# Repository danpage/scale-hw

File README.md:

# [SCALE](http://www.github.com/danpage/scale): hardware-oriented material

<!--- -------------------------------------------------------------------- --->

## Concept

The equipment used for a typical 
[side-channel attack](http://en.wikipedia.org/wiki/Side-channel_attack)
based on
[power analysis](http://en.wikipedia.org/wiki/Power_analysis)
might resemble the following:

```
                                                                   .... +-------------+
                                                                  /     | SCALE       |
+-------------+         +-------------+   trigger  +-------------+      | target      |
| control     |   USB   | acquisition | <--------- | target      |      | board       |
| platform    | <-----> | platform    |   signal   | platform    |      +-------------+
|             |         |             | <--------- |             |      | SCALE       |
+-------------+         +-------------+            +-------------+      | host        |
      ^                                                  ^        \     | board       |   
      |           USB                                    |         .... +-------------+
      +--------------------------------------------------+
```

The basic idea is that

- the target      platform represents the device under attack,
  or the
  [Device Under Test (DUT)](http://en.wikipedia.org/wiki/Device_under_test)
  in more common terms,

- the acquisition platform represents a   device, e.g., an
  [oscilloscope](http://en.wikipedia.org/wiki/Oscilloscope),
  to capture a signal from the target platform (under control of a trigger)
  and relay it to the control platform,

- the control     platform represents a workstation, which orchestrates the 
  attack by controlling the target and acquisition platforms: it will often
  repeat an acquisition loop, i.e.,

  - configure (e.g., fix the acquisition period) and initialise (e.g., arm 
    the trigger) the acquisition platform,
  - send    input     (e.g.,  plaintext) to   target      platform,
  - invoke  operation (e.g., encryption) on   target      platform,
  - receive output    (e.g., ciphertext) from target      platform,
    then,
  - receive trace                        from acquisition platform,

  to acquire a set of traces, then apply some 
  [(crypt)analytic](http://en.wikipedia.org/wiki/Cryptanalysis) 
  technique to them in order to recover information.

None of the above is an unreasonable expectation within the context of a 
research-oriented lab. but may present challenges in a teaching-oriented
alternative.  For example, particularly at scale, it may be that

- the 
  [Total Cost of Ownership (TCO)](http://en.wikipedia.org/wiki/Total_cost_of_ownership),
  i.e., capital investment plus maintenance, 
- the domain-specific requirements on 
  [Commercial Off-The-Shelf (COTS)](http://en.wikipedia.org/wiki/Commercial_off-the-shelf)
  target boards, such as the need to insert a shunt resistor into the 
  power rail,
- the need to expose at least some
  [EE](http://en.wikipedia.org/wiki/Electrical_engineering)-style 
  detail to students without a suitable background,

prevent such an approach being viable (or make it less effective).

This repo. captures a suite of 
bespoke, hardware-based target platform designs:
when combined with suitable control and acquisition platforms, it offers
a real, albeit sanitised "kit" for learning about side-channel attacks.
It has a strict remit, namely educational use (e.g., as a lab. exercise 
or assignment), which to some extent determines goals, design decisions, 
and, ultimately, the content.

<!--- -------------------------------------------------------------------- --->

## Quickstart

- Install any pre-requisites, e.g., support for
  [Git Large File Storage (LFS)](http://git-lfs.github.com/)
  (without this, some content will appear as a set of pointers to data vs. the data itself).

- Clone the repo.

  ```sh
  git clone https://github.com/danpage/scale-hw.git ./scale-hw
  cd ./scale-hw
  git submodule update --init --recursive
  source ./bin/conf.sh
  ```

- Create and populate a suitable Python
  [virtual environment](https://docs.python.org/3/library/venv.html)
  based on 
  [`${REPO_HOME}/requirements.txt`](./requirements.txt) 
  by executing
   
  ```sh
  make venv
  ```
   
  then activate it by executing
   
  ```sh
  source ${REPO_HOME}/build/venv/bin/activate
  ``` 

- Select a target board, e.g., by setting the environment variable

  ```sh
  export TARGET="lpc1313fbd48"
  ```

- Build the material 
  by executing

  ```sh
  make --directory="${REPO_HOME}/src/scale/target/${TARGET}" build
  ```

- Make use of the material in

  ```sh
  ${REPO_HOME}/build/${TARGET}
  ```

  e.g.,

  - build   the example:

    ```sh
    make --directory="${REPO_HOME}/src/scale/example" --file="${REPO_HOME}/build/${TARGET}/lib/scale.mk" PROJECT="example" BSP="${REPO_HOME}/build/${TARGET}" USB="/dev/ttyUSB0" build
    ```

  - program the example (i.e., execute it on physical hardware):

    ```sh
    make --directory="${REPO_HOME}/src/scale/example" --file="${REPO_HOME}/build/${TARGET}/lib/scale.mk" PROJECT="example" BSP="${REPO_HOME}/build/${TARGET}" USB="/dev/ttyUSB0" program
    ```

  - emulate the example (i.e., execute it on  virtual hardware):

    ```sh
    make --directory="${REPO_HOME}/src/scale/example" --file="${REPO_HOME}/build/${TARGET}/lib/scale.mk" PROJECT="example" BSP="${REPO_HOME}/build/${TARGET}" USB="/dev/ttyUSB0" emulate
    ```

<!--- -------------------------------------------------------------------- --->

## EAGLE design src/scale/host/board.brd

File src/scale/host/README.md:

# [SCALE](http://www.github.com/danpage/scale): hardware-oriented material (host board)

<!--- -------------------------------------------------------------------- --->

## Hardware 

Revision | Prototype                                                                                                 | PCB                                                                                           | Design files                                                                                                                                                                                                                 |
:------: | :-------------------------------------------------------------------------------------------------------: | :-------------------------------------------------------------------------------------------: | :--------------------------------------------------------------------------------------------------------------------------------------------------------------------------------------------------------------------------: |
C.1      |  |  | [schematic](./board.sch) (plus [PDF](./board.pdf)), [board](./board.brd), [BOM](./board.csv), [OSH Park (PCB)](http://www.oshpark.com/shared_projects/F13RPtpf), [Octopart (BOM)](http://www.octopart.com/bom-tool/LBFQutEU) |

- All communication with a control platform is performed via a
  [USB](http://en.wikipedia.org/wiki/USB)-to-[UART](http://en.wikipedia.org/wiki/Universal_asynchronous_receiver/transmitter)
  bridge, namely an
  [FTDI FT232RL](http://www.ftdichip.com/Support/Documents/DataSheets/ICs/DS_FT232R.pdf)
  (which ultimately connects to `DUT_RXD` and `DUT_TXD`).
  The surrounding design

  - basically matches the
    [SparkFun FTDI Basic Breakout](http://cdn.sparkfun.com/datasheets/BreakoutBoards/FTDI%20Basic-v22-3.3V.pdf),
    but includes a polyfuse (the breadboard prototype seems to pull about
    30 mA @ 3.3V),

  - differs from Figure 7.4 (page 31) of FT232RL datasheet wrt. both the 
    capacitors, and lack of ferrite bead.

- Both `DUT_RST` and `DUT_GPI` are connected to
  [SPST switches](http://en.wikipedia.org/wiki/Switch)
  switches.
  The surrounding design is motivated by 
  [Arduino UNO](http://www.arduino.cc/en/uploads/Main/arduino-uno-schematic.pdf),
  replacing `GND` with `UART_DTR` on the non-switch side of the capacitor
  to allow a programmer, e.g., `avrdude`, to perform a "remote reset".

- The center pin of `H.J2` ultimately supplies power the target board via 
  `DUT_VCC`: a jumper can be used to select between

  - a   5 V supply stemming from the FT232RL,
    or
  - a 3.3 V supply stemming from the FT232RL,

  or, by default (i.e., with no jumper), an external power supply which
  is provided via the labelled SMA connector and hence `PSU`.

- A signal is acquired from either `DUT_VCC` or `DUT_SIGI`, depending on
  `H.J4`, before being processed by a pipeline of components and produced
  via `DUT_SIGO`.

  - The pipeline includes a 
    100 ohm shunt resistor,
    which can be enabled or disabled using `H.J3`.

  - The pipeline includes a
    [Low Noise Amplifier (LNA)](http://en.wikipedia.org/wiki/Low-noise_amplifier),
    namely an
    [NXP BGA2801](http://www.nxp.com/documents/data_sheet/BGA2801.pdf),
    which can be enabled or disabled using `H.J5`.
    The surrounding design is basically the same as the
    [ChipWhisperer LNA module](http://wiki.newae.com/CW502_Low_Noise_Amplifier),
    which, in turn, is basically the same as the NXP reference design in
    Figure 1 (page 4) of the BGA2801 datasheet.
  
  - The pipeline includes a
    [low-pass filter](http://en.wikipedia.org/wiki/Low-pass_filter);
    which can be enabled or disabled using `H.J6`.
    The surrounding design is based in a "pi-section" structure, i.e.,
  
    ```
                 L
      ----o---8888888---o----
          |             |
          = C/2         = C/2
          |             |
         GND           GND
    ```
  
    where we select
    L   =  10.0 uH
    and
    C/2 =   1.5 nF
    to produce roughly a 2.6 MHz cut-off.

- `DUT_SCL` and `DUT_SDA` are connected to three
  [Atmel CryptoAuthentication](http://www.atmel.com/products/security-ics/cryptoauthentication)
  I2C peripherals, 
  which can be enabled or disabled using `H.J7`.
  More specifically, those peripherals are one each of

  - [ATAES132A](http://www.atmel.com/Images/Atmel-8914-CryptoAuth-ATAES132A-Datasheet.pdf),
  - [ATSHA204A](http://www.atmel.com/images/Atmel-8885-CryptoAuth-ATSHA204A-Datasheet.pdf),
    and
  - [ATECC508A](http://www.atmel.com/Images/Atmel-8923S-CryptoAuth-ATECC508A-Datasheet-Summary.pdf),

  that offer hardware-backed, cryptography-related functionality and
  some amount of generic 
  [EEPROM](http://en.wikipedia.org/wiki/EEPROM)
  storage.

<!--- -------------------------------------------------------------------- --->

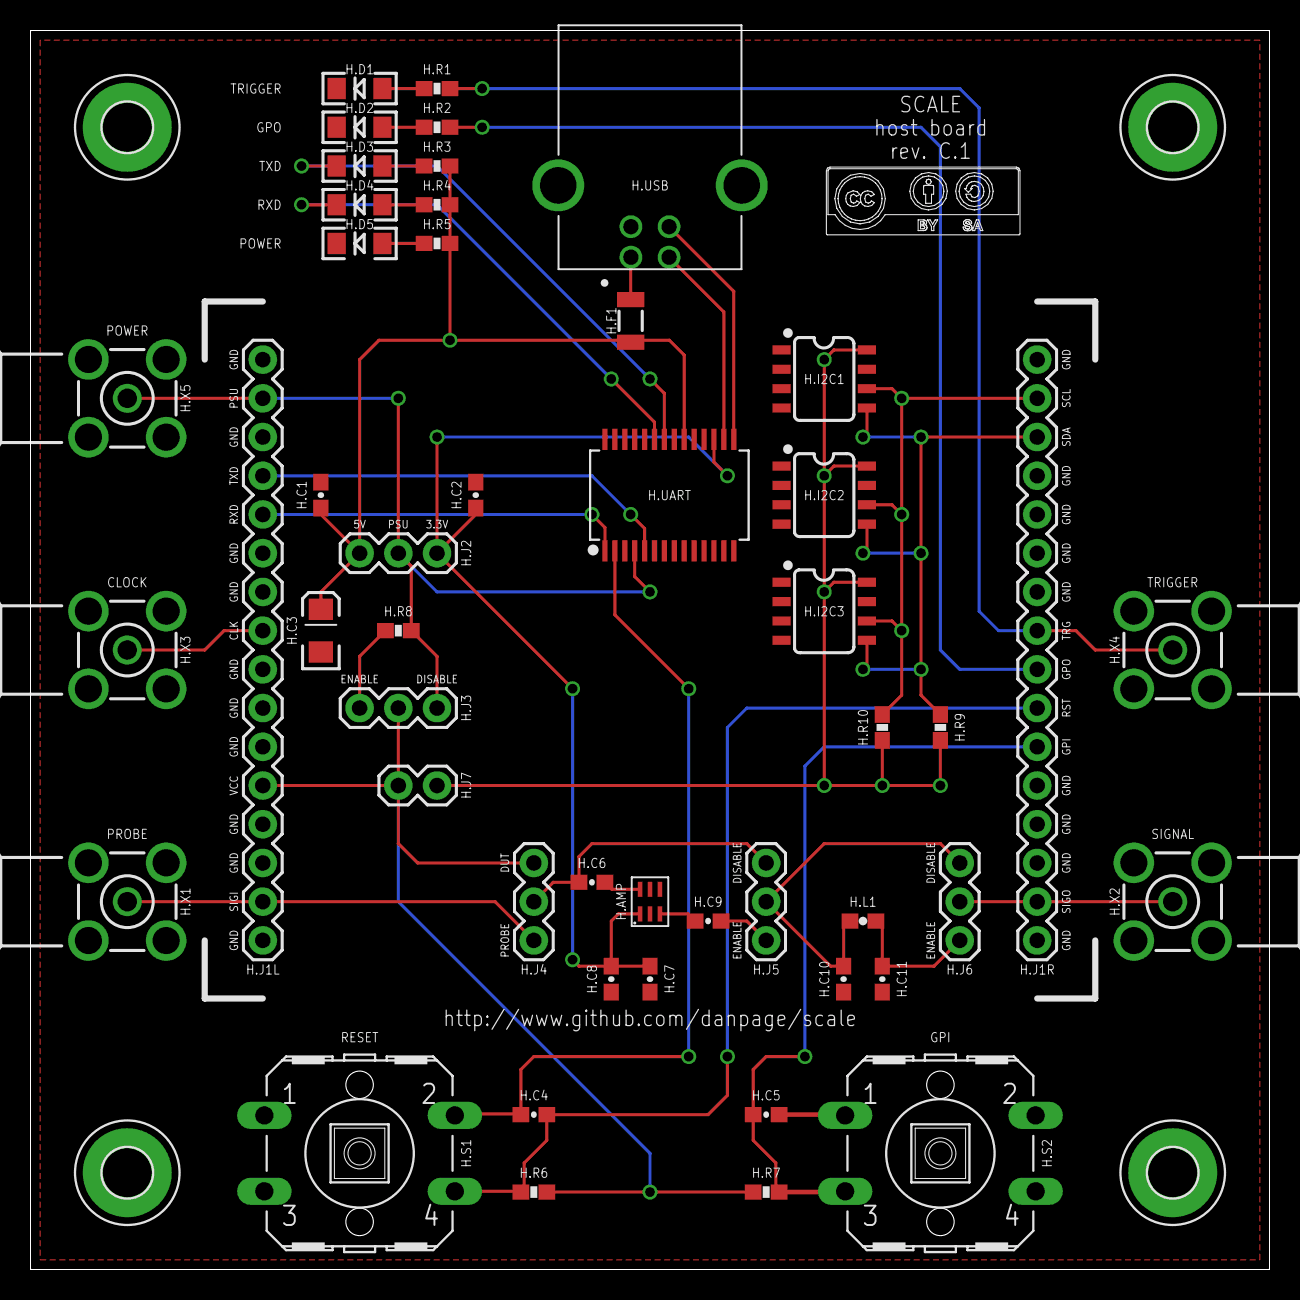
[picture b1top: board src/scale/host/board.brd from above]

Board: 2 copper layers, 81.3 x 81.3 mm, 53 parts (0 on the bottom side), 35 nets.

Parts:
H.AMP: BGA2801; SOT363
H.C1, H.C2, H.C4, H.C5: 0.1 uF; 0603-CAP
H.C3: 10 uF; EIA3216
H.C6, H.C9: 100 nF = 0.1 uF; 0603-CAP
H.C7: 4.7 uF; 0603-CAP
H.C8: 22 nF = 0.022 uF; 0603-CAP
H.C10, H.C11: 1.5 nF = 1500 pF; 0603-CAP
H.D1, H.D2, H.D5: APT3216SGC; LED-1206
H.D3, H.D4: APT3216YC; LED-1206
H.F1: 1206L025YR; PTC-1206
H.H1, H.H2, H.H3, H.H4: MOUNT-PAD-ROUND3.2; 3,2-PAD
H.I2C1: ATAES132A-SHER; SO08
H.I2C2: ATSHA204A-SSHDA; SO08
H.I2C3: ATECC108A-SSHDA; SO08
H.J1L, H.J1R: 1X16
H.J2, H.J3, H.J4, H.J5, H.J6: 1X03@1
H.J7: 1X02
H.L1: 10 uH; 0603
H.R1, H.R2, H.R3, H.R4, H.R5: 1k ohm; 0603-RES
H.R6, H.R7: 10k ohm; 0603-RES
H.R8: 100 ohm; 0603-RES
H.R9, H.R10: 3.9k ohm; 0603-RES
H.S1, H.S2: B3F-40XX
H.UART: FT232RLSSOP; SSOP28DB
H.USB: 61729-1011BLF; FCI_61729-1011BLF
H.X1, H.X2, H.X3, H.X4, H.X5: BU-SMA-H

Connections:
3.3V: H.AMP.1, H.C2.2, H.C7.2, H.C8.2, H.J2.1, H.UART.17
5V: H.C1.2, H.C3.A, H.F1.2, H.J2.3, H.R3.1, H.R4.1, H.R5.1, H.UART.20
AMP: H.AMP.3, H.C9.2
DUT_CLK: H.J1L.9, H.X3.1
DUT_GPI: H.C5.2, H.J1R.6, H.R7.1, H.S2.3
DUT_GPO: H.J1R.8, H.R2.1
DUT_RST: H.C4.2, H.J1R.7, H.R6.1, H.S1.4
DUT_RXD: H.J1L.12, H.UART.1
DUT_SCL: H.I2C1.6, H.I2C2.6, H.I2C3.6, H.J1R.15, H.R10.1
DUT_SDA: H.I2C1.5, H.I2C2.5, H.I2C3.5, H.J1R.14, H.R9.1
DUT_SIGI: H.J1L.2, H.J4.3, H.X1.1
DUT_SIGO: H.J1R.2, H.J6.2, H.X2.1
DUT_TRG: H.J1R.9, H.R1.1, H.X4.1
DUT_TXD: H.J1L.13, H.UART.5
DUT_VCC: H.J1L.5, H.J3.2, H.J4.1, H.J7.1, H.R6.2, H.R7.2
GND: H.AMP.2, H.AMP.4, H.AMP.5, H.C1.1, H.C2.1, H.C3.C, H.C5.1, H.C7.1, H.C8.1, H.C10.1, H.C11.1, H.D1.C, H.D2.C, H.D5.C, H.H1.B3,2, H.H2.B3,2, H.H3.B3,2, H.H4.B3,2, H.I2C1.4, H.I2C2.4, H.I2C3.4, H.J1L.1, H.J1L.3, H.J1L.4, H.J1L.6, H.J1L.7, H.J1L.8, H.J1L.10, H.J1L.11, H.J1L.14, H.J1L.16, H.J1R.1, H.J1R.3, H.J1R.4, H.J1R.5, H.J1R.10, H.J1R.11, H.J1R.12, H.J1R.13, H.J1R.16, H.S2.1, H.UART.7, H.UART.18, H.UART.21, H.UART.25, H.UART.26, H.USB.4, H.USB.S1, H.USB.S2, H.X1.2, H.X1.3, H.X1.4, H.X1.5, H.X2.2, H.X2.3, H.X2.4, H.X2.5, H.X3.2, H.X3.3, H.X3.4, H.X3.5, H.X4.2, H.X4.3, H.X4.4, H.X4.5, H.X5.2, H.X5.3, H.X5.4, H.X5.5
unnamed: H.D5.A, H.R5.2
unnamed: H.D4.A, H.R4.2
unnamed: H.D3.A, H.R3.2
unnamed: H.D1.A, H.R1.2
unnamed: H.D2.A, H.R2.2
unnamed: H.UART.16, H.USB.2
unnamed: H.UART.15, H.USB.3
unnamed: H.C9.1, H.J5.1
unnamed: H.C11.2, H.J6.1, H.L1.2
unnamed: H.C10.2, H.J5.2, H.J6.3, H.L1.1
unnamed: H.J3.1, H.R8.2
unnamed: H.F1.1, H.USB.1
unnamed: H.I2C1.8, H.I2C2.8, H.I2C3.8, H.J7.2, H.R9.2, H.R10.2
unnamed: H.AMP.6, H.C6.1
unnamed: H.C6.2, H.J4.2, H.J5.3
PSU: H.J1L.15, H.J2.2, H.J3.3, H.R8.1, H.UART.4, H.X5.1
UART_DTR: H.C4.1, H.S1.2, H.UART.2
UART_RXDLED: H.D3.C, H.UART.22
UART_TXDLED: H.D4.C, H.UART.23

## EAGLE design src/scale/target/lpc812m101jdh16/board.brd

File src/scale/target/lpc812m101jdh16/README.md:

# [SCALE](http://www.github.com/danpage/scale): hardware-oriented material (target board: lpc812m101jdh16)

<!--- -------------------------------------------------------------------- --->

## Hardware 

Revision | Prototype                                                                                                 | PCB                                                                                           | Design files                                                                                                                                                                                                                 |
:------: | :-------------------------------------------------------------------------------------------------------: | :-------------------------------------------------------------------------------------------: | :--------------------------------------------------------------------------------------------------------------------------------------------------------------------------------------------------------------------------: |
C.1      |  |  | [schematic](./board.sch) (plus [PDF](./board.pdf)), [board](./board.brd), [BOM](./board.csv), [OSH Park (PCB)](http://www.oshpark.com/shared_projects/ANKAjSGc), [Octopart (BOM)](http://www.octopart.com/bom-tool/BlsVKS9M) |

- The target board houses a
  32-bit ARM Cortex-M0+
  core, which acts as the 
  [DUT](http://en.wikipedia.org/wiki/Device_under_test).
  More specifically, the DUT is a
  16-pin, TSSOP-format
  [NXP lpc812m101jdh16](http://www.nxp.com/documents/data_sheet/LPC81XM.pdf)
  IC (the
  [user manual](http://www.nxp.com/documents/user_manual/UM10601.pdf)
  for which is more detailed); 
  it has 16 kB FLASH and 4 kB SRAM memory.

- Relevant aspects of the DUT pin-out, and their relationship with the
  target board schematic, are illustrated below:

  ```
                        +-----------------+
                       1|                 |16 = PIO0_0  = DUT_RXD
  DUT_GPI = PIO0_12 =  2|                 |15 = PIO0_6  = DUT_TRG
  DUT_RST =            3|                 |14 = PIO_7   = DUT_GPO
  DUT_TXD = PIO0_4  =  4| lpc812m101jdh16 |13 = GND     = DUT_GND
            SWCLK   =  5|                 |12 = VCC     = DUT_VCC
            SWDIO   =  6|                 |11 = XTALIN  = DUT_XTAL1
  DUT_SCL =            7|                 |10 = XTALOUT = DUT_XTAL2
  DUT_SDA =            8|                 |9 
                        +-----------------+
  ```

- The core voltage required on `DUT_VCC` is 3.3 V: 
  `H.J2` must therefore be set appropriately.

- The core has a
  12 MHz
  internal oscillator, but can be driven by either 

  - an external clock source provided (on `DUT_XTAL1` and `DUT_XTAL2` via `DUT_CLK`),
    or
  - 16 MHz external crystal housed on the target board.

  To support these, some extra, carefully selected capacitors
  are required: the DUT
  [datasheet](http://www.nxp.com/documents/data_sheet/LPC81XM.pdf)
  specifies that for C_L = 10 pF crystal load capacitance,

  | Type    | Reference             | XTALIN  (`DUT_XTAL1`)                                  | XTALOUT (`DUT_XTAL2`)   |
  |:-------:|:---------------------:|:------------------------------------------------------:|:-----------------------:|
  | Crystal | Figure 37, Table  26  | C_X1 =  18 pF = 0.018 nF                               | C_X2 = 18 pF = 0.018 nF |
  | Clock   | Figure 36             | C_i  = 100 pF = 0.100 nF <br/> C_g = 300 pF = 0.300 nF | disconnected            |

  In the latter case we want 200 mV < f * V_RMS < 1000 mV, where
  f = C_i / ( C_i + C_g ),
  so if we pick V_peak = 3.3 V, then because
  V_RMS  = V_peak * \sqrt{duty cycle}
         = 3.3    * \sqrt{1/2}
        ~= 2.3
  then f = 1/4 and hence C_g = 300 pF does the job.

- Specific pins on the DUT are made accessible via `T.J2` in order to
  allow attachment of a hardware programmer or debugger.
  For example, it is possible to attach a
  [Segger J-Link](http://www.segger.com/admin/uploads/productDocs/UM08001_JLink.pdf)
  to the DUT by connecting the 20-pin header as follows

  ```
              +--------+
  DUT_VCC =  1|        |2
             3|        |4  = DUT_GND
             5|        |6
    SWDIO =  7|        |8
    SWCLK =  9| J-Link |10
            11|        |12
            13|        |14
  DUT_RST = 15|        |16
            17|        |18
            19|        |20
              +--------+
  ```
               
  and thereby make use of Serial Wire Debug (SWD).

<!--- -------------------------------------------------------------------- --->

## Software

- Under
  [Ubuntu](http://www.ubuntu.com)-based
  Linux, for example, 
  the development dependencies can be installed 
  by issuing the command

  ```
  sudo apt-get install gcc-arm-none-eabi lpc21isp
  ```

  That said, some versions of this 
  [Ubuntu packaged](https://launchpad.net/ubuntu/+source/gcc-arm-none-eabi) 
  tool-chain have known issues 
  (see, e.g., [1](https://bugs.launchpad.net/gcc-arm-embedded/+bug/1722849)
              or
              [2](https://bugs.launchpad.net/gcc-arm-embedded/+bug/1502611));
  take care, or, as an alternative, consider using an 
  ["official" release](https://developer.arm.com/tools-and-software/open-source-software/developer-tools/gnu-toolchain)
  directly from ARM instead.

- A pre-installed 
  [bootloader](http://en.wikipedia.org/wiki/Booting)
  allows programming of the DUT over USB;
  this means
  [lpc21isp](http://sourceforge.net/projects/lpc21isp)
  can be used as is.  
  The GPI switch on the host board will activate the bootloader during 
  reset, so the steps required are basically

  - execute lpc2isp, which then waits,
  - press and hold the (right-hand) GPI   switch,  
  - press and hold the  (left-hand) reset switch,
  - release        the  (left-hand) reset switch,
  - transfer via lpc2isp starts,
  - release        the (right-hand) GPI   switch,
  - transfer via lpc2isp finishes.

- Note that the default BSP configuration is conservative, st.

  - the
    internal 12 MHz oscillator
    is used as the clock source,
    meaning `T.J3` and `T.J4` on the target board 
    are irrelevant,
  - the 
    UART 
    interface operates per 9600/8N1,
  - the
    I2C
    interface operates per 100 kHz standard mode.

<!--- -------------------------------------------------------------------- --->

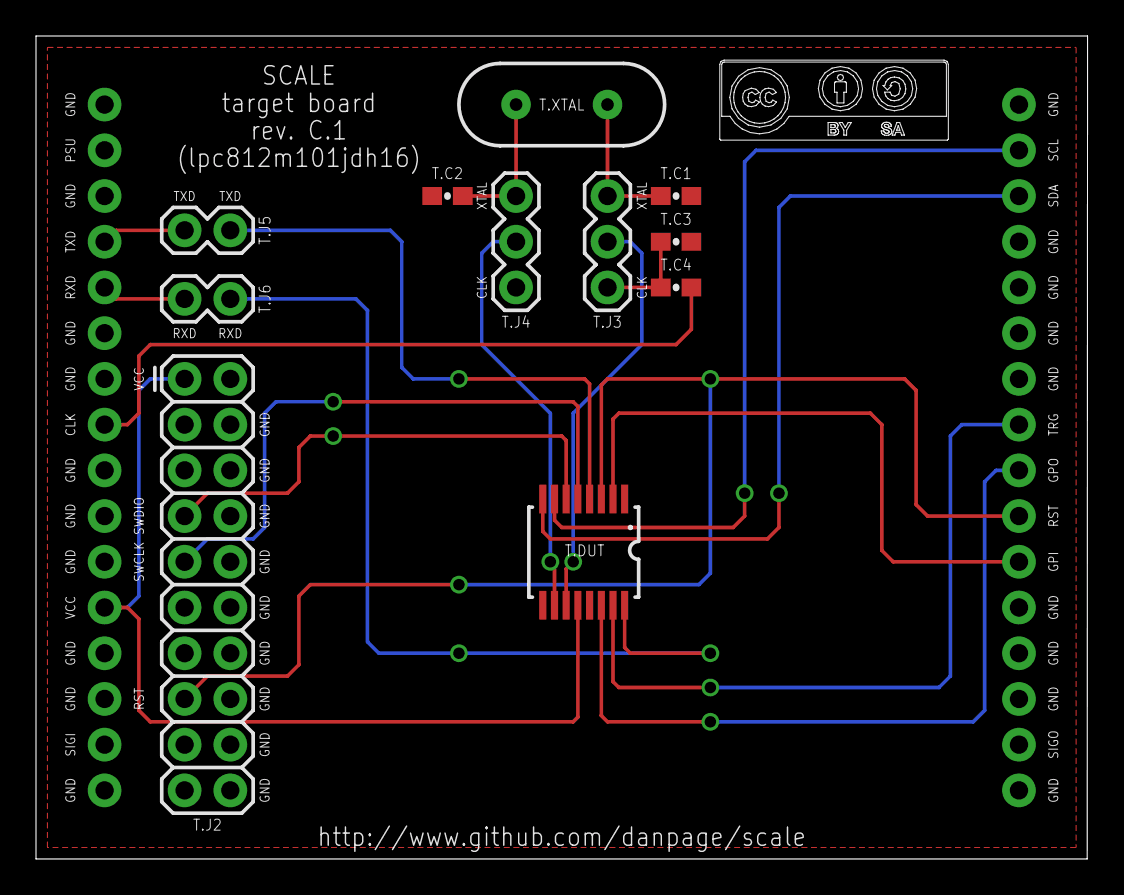
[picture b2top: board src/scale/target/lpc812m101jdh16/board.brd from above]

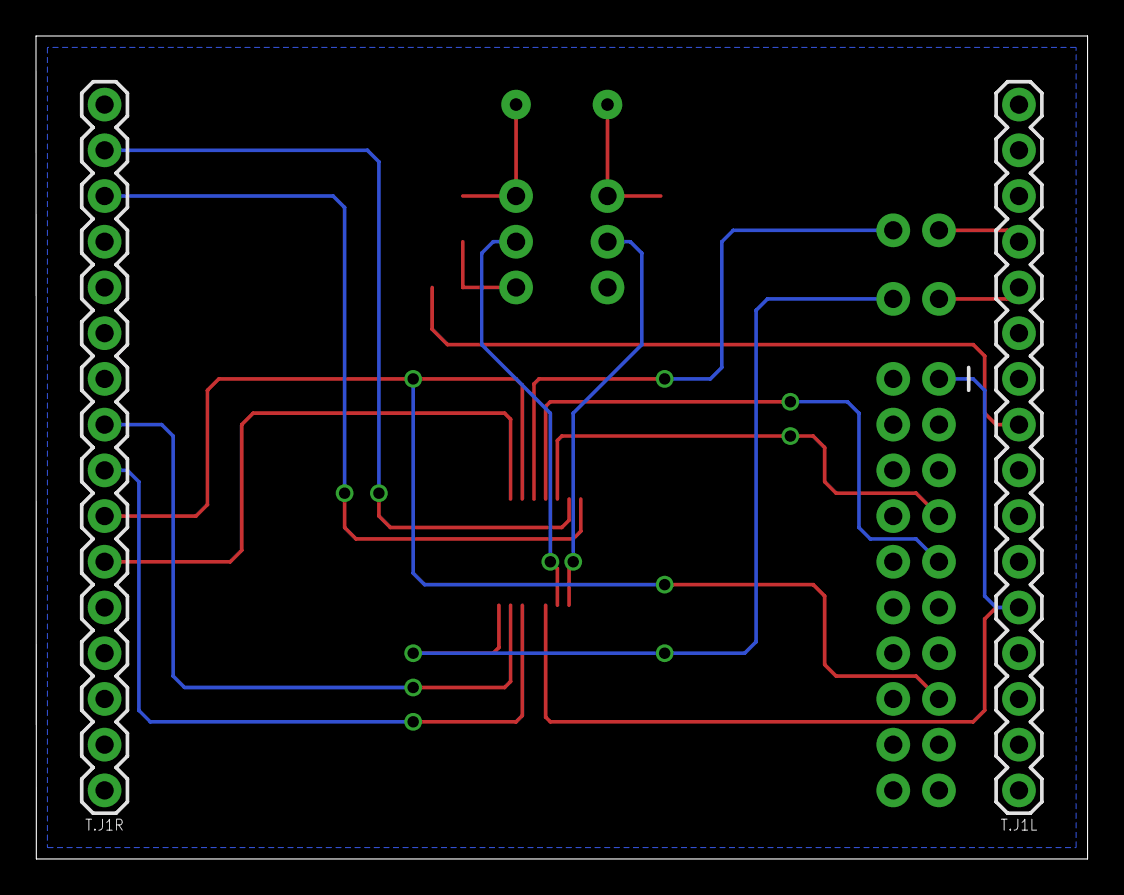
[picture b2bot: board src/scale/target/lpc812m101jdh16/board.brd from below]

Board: 2 copper layers, 58.4 x 45.7 mm, 13 parts (2 on the bottom side), 20 nets.

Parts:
T.C1, T.C2: 0.018 nF = 18 pF; 0603-CAP
T.C3: 0.3 nF = 300 pF; 0603-CAP
T.C4: 0.1 nF = 100 pF; 0603-CAP
T.DUT: LPC812M101JDH16; TSSOP16
T.J1L, T.J1R: 1X16
T.J2: 2X10
T.J3, T.J4: 1X03
T.J5, T.J6: 1X02
T.XTAL: 16 Mhz; HC49US

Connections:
DUT_CLK: T.C4.2, T.J1L.9
DUT_GPI: T.DUT.2, T.J1R.6
DUT_GPO: T.DUT.14, T.J1R.8
DUT_RST: T.DUT.3, T.J1R.7, T.J2.15
DUT_RXD: T.J1L.12, T.J6.1
DUT_SCL: T.DUT.7, T.J1R.15
DUT_SDA: T.DUT.8, T.J1R.14
DUT_SWCLK: T.DUT.5, T.J2.9
DUT_SWDIO: T.DUT.6, T.J2.7
DUT_TRG: T.DUT.15, T.J1R.9
DUT_TXD: T.J1L.13, T.J5.1
DUT_VCC: T.DUT.12, T.J1L.5, T.J2.1
DUT_XTAL1: T.DUT.11, T.J3.2
DUT_XTAL2: T.DUT.10, T.J4.2
GND: T.C1.1, T.C2.1, T.C3.1, T.DUT.13, T.J1L.1, T.J1L.3, T.J1L.4, T.J1L.6, T.J1L.7, T.J1L.8, T.J1L.10, T.J1L.11, T.J1L.14, T.J1L.16, T.J1R.1, T.J1R.3, T.J1R.4, T.J1R.5, T.J1R.10, T.J1R.11, T.J1R.12, T.J1R.13, T.J1R.16, T.J2.4, T.J2.6, T.J2.8, T.J2.10, T.J2.12, T.J2.14, T.J2.16, T.J2.18, T.J2.20
unnamed: T.C1.2, T.J3.1, T.XTAL.2
unnamed: T.C2.2, T.J4.1, T.XTAL.1
unnamed: T.C3.2, T.C4.1, T.J3.3
unnamed: T.DUT.4, T.J5.2
unnamed: T.DUT.16, T.J6.2

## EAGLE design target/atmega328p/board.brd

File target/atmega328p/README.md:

# [SCALE](http://www.github.com/danpage/scale): hardware-oriented offshoot (target board: atmega328p)

<!--- -------------------------------------------------------------------- --->

## Hardware 

Revision | Prototype                                                                                                 | PCB                                                                                           | Design files                                                                                                                                                                                                                 |
:------: | :-------------------------------------------------------------------------------------------------------: | :-------------------------------------------------------------------------------------------: | :--------------------------------------------------------------------------------------------------------------------------------------------------------------------------------------------------------------------------: |
C.1      |  |  | [schematic](./board.sch) (plus [PDF](./board.pdf)), [board](./board.brd), [BOM](./board.csv), [OSH Park (PCB)](http://www.oshpark.com/shared_projects/YczSc1Wc), [Octopart (BOM)](http://www.octopart.com/bom-tool/CbDjCRPB) |

- The target board houses an 
  8-bit Atmel ATmega
  core, which acts as the 
  [DUT](http://en.wikipedia.org/wiki/Device_under_test).
  More specifically, the DUT is a
  28-pin, DIP-format
  [Atmel atmega328p](http://www.atmel.com/Images/Atmel-42735-8-bit-AVR-Microcontroller-ATmega328-328P_Datasheet.pdf)
  IC; 
  it has 32 kB FLASH and 2 kB SRAM memory.

- Relevant aspects of the DUT pin-out, and their relationship with the
  target board schematic, are illustrated below:

  ```
                       +------------+
  DUT_RST   = PC6  =  1|            |28 =         DUT_SCL
  DUT_RXD   = PD0  =  2|            |27 =         DUT_SDA
  DUT_TXD   = PD1  =  3|            |26
  DUT_GPI   = PD2  =  4|            |25
                      5|            |24
                      6|            |23
  DUT_VCC   = VCC  =  7| ATmega328p |22 =  GND
              GND  =  8|            |21
  DUT_XTAL1 = PB6  =  9|            |20 =  VCC  = DUT_VCC
  DUT_XTAL2 = PB7  = 10|            |19 =  SCK
                     11|            |18 =  MISO
                     12|            |17 =  MOSI
  DUT_GPO   = PD7  = 13|            |16
  DUT_TGR   = PB0  = 14|            |15
                       +------------+
  ```

- The core voltage required on `DUT_VCC` is 5 V: 
  `H.J2` must therefore be set appropriately.

- The core has a
  1 MHz
  internal clock source, but can be driven by either 

  - an external clock source provided (on `DUT_XTAL1` and `DUT_XTAL2` via `DUT_CLK`),
    or
  - 16 MHz external crystal housed on the target board.

  To support these, some extra, carefully selected capacitors
  are required: the DUT
  [datasheet](http://www.atmel.com/Images/Atmel-42735-8-bit-AVR-Microcontroller-ATmega328-328P_Datasheet.pdf)
  specifies that

  | Type    | Reference   | XTALIN  (`DUT_XTAL1`)                                  | XTALOUT (`DUT_XTAL2`)   |
  |:-------:|:-----------:|:------------------------------------------------------:|:-----------------------:|
  | Crystal | Figure 13-2 | C1   =  22 pF = 0.022 nF                               | C2   = 22 pF = 0.022 nF |
  | Clock   | Figure 13-3 | no capacitors required                                 | disconnected            |

- Specific pins on the DUT are made accessible via `T.J2` in order to
  allow attachment of a hardware programmer or debugger.
  For example, it is possible to attach an
  [Atmel AVRISP mkII](http://www.atmel.com/Images/Atmel-42093-AVR-ISP-mkII_UserGuide.pdf)
  (or indeed *any* low-cost ISP-based programmer)
  to the DUT by connecting the 6-pin header as follows

  ```
             +-----+
     MISO = 1|     |2 = DUT_VCC
      SCK = 3| ISP |4 = MOSI
  DUT_RST = 5|     |6 = DUT_GND
             +-----+
  ```

  taking care wrt. pin 2.  Some programmers will sense a core voltage
  from this pin, some will *supply* a core voltage using it, some can
  be configured to do either: by whatever means (e.g., disconnecting
  the pin, or configuring the programmer), do *not* use it supply a 
  core voltage.

<!--- -------------------------------------------------------------------- --->

## Software

- Under
  [Ubuntu](http://www.ubuntu.com)-based
  Linux, for example, 
  the development dependencies can be installed 
  by issuing the command

  ```
  sudo apt-get install gcc-avr avrdude
  ```

- We assume an Arduino-based
  [bootloader](http://en.wikipedia.org/wiki/Booting),
  such as
  [Optiboot](http://www.github.com/Optiboot/optiboot),
  has been pre-installed to allow programming of the DUT over USB;
  this means
  [avrdude](http://www.nongnu.org/avrdude)
  can be used as is,
  as can the Arduino
  [IDE](http://www.arduino.cc/en/main/software)
  if you prefer.

- Note that the default BSP configuration is conservative, st.

  - the
    external 16 MHz crystal
    is used as the clock source,
    meaning `T.J3` and `T.J4` on the target board 
    must be set appropriately,
  - the 
    UART 
    interface operates per 9600/8N1,
  - the
    I2C
    interface operates per 100 kHz standard mode.

<!--- -------------------------------------------------------------------- --->

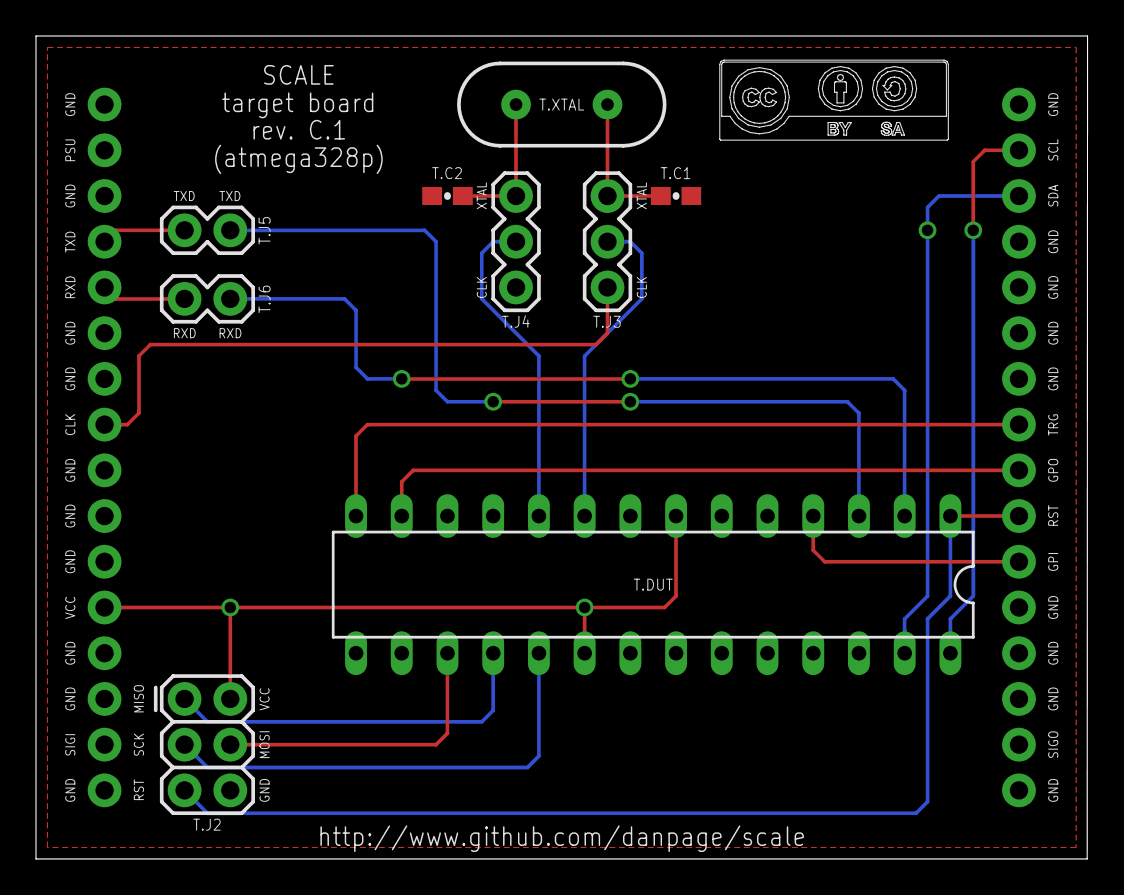
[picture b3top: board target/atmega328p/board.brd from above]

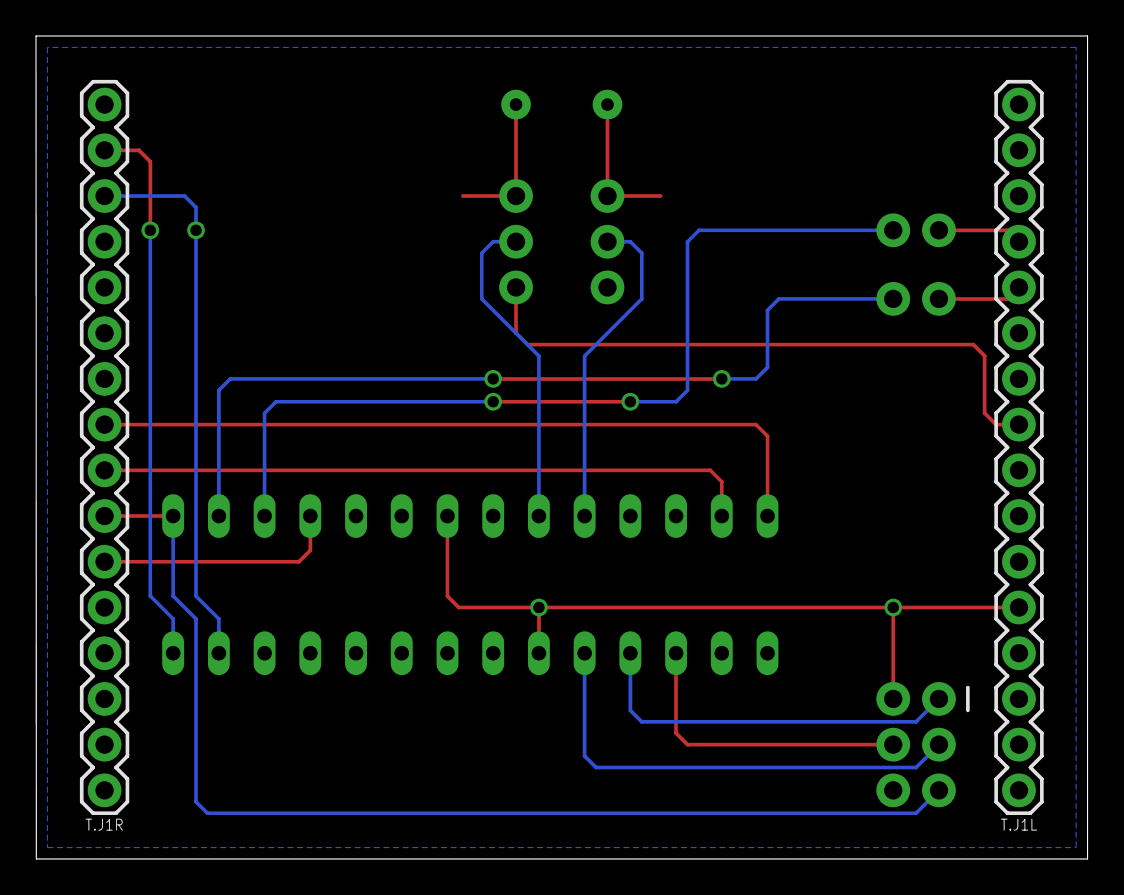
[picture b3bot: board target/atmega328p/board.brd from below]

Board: 2 copper layers, 58.4 x 45.7 mm, 11 parts (2 on the bottom side), 20 nets.

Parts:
T.C1, T.C2: 0.022 nF = 22 pF; 0603-CAP
T.DUT: DIL28-3
T.J1L, T.J1R: 1X16
T.J2: 2X3
T.J3, T.J4: 1X03
T.J5, T.J6: 1X02
T.XTAL: 16 Mhz; HC49US

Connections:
DUT_CLK: T.J1L.9, T.J3.3
DUT_GPI: T.DUT.4, T.J1R.6
DUT_GPO: T.DUT.13, T.J1R.8
DUT_MISO: T.DUT.18, T.J2.1
DUT_MOSI: T.DUT.17, T.J2.4
DUT_RST: T.DUT.1, T.J1R.7, T.J2.5
DUT_RXD: T.J1L.12, T.J6.1
DUT_SCK: T.DUT.19, T.J2.3
DUT_SCL: T.DUT.28, T.J1R.15
DUT_SDA: T.DUT.27, T.J1R.14
DUT_TRG: T.DUT.14, T.J1R.9
DUT_TXD: T.J1L.13, T.J5.1
DUT_VCC: T.DUT.7, T.DUT.20, T.J1L.5, T.J2.2
DUT_XTAL1: T.DUT.9, T.J3.2
DUT_XTAL2: T.DUT.10, T.J4.2
GND: T.C1.1, T.C2.1, T.DUT.8, T.DUT.22, T.J1L.1, T.J1L.3, T.J1L.4, T.J1L.6, T.J1L.7, T.J1L.8, T.J1L.10, T.J1L.11, T.J1L.14, T.J1L.16, T.J1R.1, T.J1R.3, T.J1R.4, T.J1R.5, T.J1R.10, T.J1R.11, T.J1R.12, T.J1R.13, T.J1R.16, T.J2.6
unnamed: T.C1.2, T.J3.1, T.XTAL.2
unnamed: T.C2.2, T.J4.1, T.XTAL.1
unnamed: T.DUT.3, T.J5.2
unnamed: T.DUT.2, T.J6.2

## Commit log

2018-07-25 Absorbed hyphen into ${GCC_PREFIX} to allow for empty prefix if/where required
2018-11-05 Update UART interface to allow blocking/non-blocking reads and writes; fixed some cases of UART configuration order, plus flush UART after configuration; minor, superficial updates (e.g., wrt. body'l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
2019-01-11 experimental support for systick (plus some reorganisation wrt. BSP and build system)
2019-01-16 moved objcopy flags into scale.conf (plus some reorgnisation of build system)
2019-05-15 Revert (i.e., remove) UART flush/drain in initialisation: turns out to be pointless, and annoying!
2019-05-15 Fix bug wrt. UART clock: stems from *main* clk, not *core* (i.e., target) clock, so need to adjust divider accordingly.
2019-05-20 Fixed typo. wrt. lpc812 GPIO symbol (see issue #1)
2019-05-20 Added some text wrt. issues with Ubuntu-packaged ARM toolchain (i.e., "use ARM release instead")
2019-05-20 Minor update to text wrt. Ubuntu-packaged ARM toolchain
2019-05-22 Added emulator, and updated build system to include support for Putty-based interaction.
2019-09-11 Added patch against OpenOCD 0.10.0 to automate solution to part ID issue.
2019-09-11 Added reference to HorrorScope.
2019-09-26 Updated Putty config. copy target to pre-create directory when need be
2019-11-14 fix typo. + tweak terminology re. I2C peripherals
2020-06-23 update objcopy flag to long version for consistency
2020-06-24 force a spin ~= halt in __start after calling main
2020-06-24 cosmetic, pedantic changes
2020-06-24 bump
2021-11-10 update README re. KiCad URL
2022-04-21 initial attempt at python3 port
2022-04-26 move
2022-06-14 update build system for out-of-tree builds
2022-06-15 some tweaks to debug emulator for python3 (wrt. bytes in memory I/O)
2022-06-15 fine tune markdown
2022-07-14 tweak makefile target names for putty (physical+emulated vs. board+emulator)
2022-07-20 switch emulator to python3; allow parameterised emulator host and port
2023-01-18 remove virtual environment versioning requirements for scipy and numpy
2023-02-27 label warning messages from make for clarity; correct spurious ifndef lpc1114fn28 case
2023-08-25 switch from pycryptodome to pycryptodomex
2023-09-20 force alignment of sections in shared assembly language
2025-09-03 bump pico-python (aka. picoscope) version
2025-09-05 bump unicorn, capstone, etc. versions
2026-01-15 relax/remove versioning in requirements.txt, which is overly constraining in some cases

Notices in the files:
parts and their libraries:
SparkFun-Connectors: Licensing: Creative Commons ShareAlike 4.0 International - https://creativecommons.org/licenses/by-sa/4.0
